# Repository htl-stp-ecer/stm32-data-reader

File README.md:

<div align="center">

# stm32-data-reader

**Raspberry Pi ↔ STM32 SPI bridge — reads sensor data and publishes it via LCM for RaccoonOS.**

> 📖 **Full documentation at [raccoon-docs.pages.dev](https://raccoon-docs.pages.dev/)**

</div>

---

This service runs on the Raspberry Pi inside the [KIPR Wombat](https://www.kipr.org/kipr/hardware-software) and acts as the hardware bridge between the STM32 microcontroller and the rest of RaccoonOS. It communicates with the STM32 over SPI, reads IMU, analog, and digital sensor data, and publishes everything onto the LCM multicast bus — where [RaccoonLib](https://github.com/htl-stp-ecer/raccoon-lib) and [botui](https://github.com/htl-stp-ecer/botui) can consume it. Motor and servo commands flow the other way: received from LCM and forwarded to the STM32.

---

## What it bridges

**Publishes (STM32 → LCM):**
- IMU — gyroscope, accelerometer, magnetometer, orientation quaternion, calibration accuracy
- Analog inputs (6 ports), digital inputs (16-bit)
- Motor back-EMF readings (4 ports)
- System — battery voltage, IMU temperature, CPU temperature

**Subscribes (LCM → STM32):**
- Motor power and stop commands (4 ports)
- Servo position commands (4 ports)
- BEMF reset, scale, and offset commands

Full channel reference: see [LCM Channels](#lcm-channels) below.

---

## Building

Reader and firmware are cross compiled for the Pi in Docker on your PC at native speed (no emulation). You only need Docker and Python 3.

```bash
python3 build.py                  # reader + firmware -> builds/stm32-data-reader_0.0_arm64.deb
python3 build.py --version 60     # release build (what CI does)
python3 build.py --test           # also build the unit tests and run them with qemu-user
python3 build.py --skip-firmware  # reuse the firmware of the last build
```

Output: `builds/stm32-data-reader_<version>_arm64.deb` (the reader, the STM32 firmware with its flash scripts, the systemd units) and `builds/manifest.json`. Measured: about 50 seconds from scratch (without cache), a few seconds with the cache.

### Local build (mock SPI, no hardware needed)

```bash
mkdir -p cmake-build-debug && cd cmake-build-debug
cmake .. -DUSE_SPI_MOCK=ON -DCMAKE_BUILD_TYPE=Debug
cmake --build . -j$(nproc)
```

| CMake option | Default | Description |
|:-------------|:--------|:------------|
| `USE_SPI_MOCK` | `ON` | Mock SPI — build and test without hardware |
| `CMAKE_BUILD_TYPE` | `Release` | `Release`, `Debug`, `RelWithDebInfo` |

---

## Deployment

### Install a release (recommended)

Each [release](https://github.com/htl-stp-ecer/stm32-data-reader/releases/latest) ships
`stm32-data-reader_<number>_arm64.deb`. `raccoon update` installs it, or on the Pi:

```bash
sudo apt install ./stm32-data-reader_<number>_arm64.deb
```

That installs the reader to `/usr/bin`, the firmware with its flash scripts to `/usr/lib/stm32-data-reader/firmware`, flashes the STM32 when the hardware is there and starts the services.

### Dev deploy (from source)

```bash
python3 deploy.py --host <your-pi-ip>     # installs builds/*.deb, flashes the firmware
```

`deploy.py` copies the `.deb` from `builds/` (made by `build.py`) to the Pi, sets `stm32-data-reader` to `dev` in `/etc/raccoon-bundle.json` (a deployed build is a custom build) and installs it with `apt`. The package installs the units, flashes the firmware and restarts the reader, so every deploy flashes the STM32 again.

### Running as a systemd service

```bash
sudo systemctl enable --now stm32_data_reader
journalctl -u stm32_data_reader -f
```

---

## Firmware

The STM32 firmware lives in `firmware/` and shares the SPI protocol header (`shared/spi/pi_buffer.h`) with the reader — single source of truth for both sides.

```bash
# Reader and firmware together, in Docker
python3 build.py

# Build firmware natively (requires gcc-arm-none-eabi)
cd firmware && mkdir -p build && cd build
cmake -G "Unix Makefiles" -DCMAKE_TOOLCHAIN_FILE=../CMake/GNU-ARM-Toolchain.cmake ..
cmake --build . -- -j$(nproc)
```

`python3 build.py` builds reader and firmware together (the firmware in `Dockerfile.firmware`). `python3 deploy.py --host <pi>` installs the package, which flashes the firmware to the STM32.

---

## Architecture

<div align="center">
  
</div>

| Component | What it does |
|:----------|:-------------|
| `Application` | Main orchestrator — lifecycle, signal handling |
| `DeviceController` | Owns SPI state: motors, servos, sensors |
| `DataPublisher` | Publishes sensor data to LCM with change detection |
| `CommandSubscriber` | Receives LCM commands and routes to DeviceController |
| `LcmBroker` | Typed publish/subscribe wrapper (PIMPL pattern) |
| `Spi` / `SpiMock` | Hardware abstraction toggled via `USE_SPI_MOCK` |

---

## LCM Channels

### Published (sensor data)

| Channel | Type | Description |
|:--------|:-----|:------------|
| `libstp/gyro/value` | `vector3f_t` | Gyroscope (rad/s) |
| `libstp/accel/value` | `vector3f_t` | Accelerometer (m/s²) |
| `libstp/mag/value` | `vector3f_t` | Magnetometer |
| `libstp/imu/quaternion` | `quaternion_t` | Orientation quaternion |
| `libstp/imu/temp/value` | `scalar_f_t` | IMU temperature (°C) |
| `libstp/cpu/temp/value` | `scalar_f_t` | CPU temperature (°C) |
| `libstp/battery/voltage` | `scalar_f_t` | Battery voltage |
| `libstp/analog/{0-5}/value` | `scalar_i32_t` | Analog sensor readings |
| `libstp/digital/{0-15}/value` | `scalar_i32_t` | Digital input states |
| `libstp/bemf/{0-3}/value` | `scalar_i32_t` | Motor back-EMF |
| `libstp/gyro/accuracy` | `scalar_i8_t` | Gyro calibration status (0–3) |
| `libstp/accel/accuracy` | `scalar_i8_t` | Accelerometer calibration status |
| `libstp/mag/accuracy` | `scalar_i8_t` | Magnetometer calibration status |
| `libstp/imu/quaternion_accuracy` | `scalar_i8_t` | Quaternion accuracy |

### Subscribed (commands)

| Channel | Type | Description |
|:--------|:-----|:------------|
| `libstp/motor/{0-3}/power_cmd` | `scalar_i32_t` | Motor power (−100 to 100) |
| `libstp/motor/{0-3}/stop_cmd` | `scalar_i32_t` | Stop motor |
| `libstp/servo/{0-3}/position_cmd` | `scalar_i32_t` | Servo position |
| `libstp/bemf/{0-3}/reset_cmd` | `scalar_i32_t` | Reset BEMF accumulator |
| `libstp/bemf/{0-3}/scale_cmd` | `scalar_f_t` | BEMF scale factor |
| `libstp/bemf/{0-3}/offset_cmd` | `scalar_f_t` | BEMF offset |
| `libstp/bemf/nominal_voltage_cmd` | `scalar_i32_t` | Nominal battery voltage |
| `libstp/system/dump_request` | `scalar_i32_t` | Request full data dump |

---

## Network setup for LCM

LCM uses UDP multicast. Enable the loopback route for local-only operation:

```bash
sudo systemctl enable --now lcm-loopback-multicast
# or manually:
sudo ip route add 239.255.76.67/32 dev lo
```

For network operation, ensure multicast is enabled and UDP port 7667 is open.

---

## Project structure

```
stm32-data-reader/
├── src/wombat/
│   ├── Application.cpp
│   ├── services/            # DataPublisher, CommandSubscriber, DeviceController
│   ├── hardware/            # Spi, SpiMock
│   ├── messaging/           # LcmBroker
│   └── core/                # Logger, Result<T>, utilities
├── include/wombat/          # Headers matching src/
├── shared/spi/pi_buffer.h   # SPI protocol (shared with STM32 firmware)
├── firmware/                # STM32 firmware source
├── lcm-messages/types/      # LCM message definitions (.lcm files)
├── systemd/                 # Service files
├── packaging/debian/        # control and maintainer scripts of the .deb
├── build.py                 # Cross-compiles reader + firmware in Docker, makes the .deb (builds/)
├── deploy.py                # Installs the .deb on a Pi (development)
├── Dockerfile               # aarch64 cross compiler for the reader
└── Dockerfile.firmware      # arm-none-eabi-gcc for the firmware
```

---

## Part of RaccoonOS

| Repository | What it is |
|:-----------|:-----------|
| [raccoon-lib](https://github.com/htl-stp-ecer/raccoon-lib) | Core robotics library — consumes LCM data published here |
| [raccoon-transport](https://github.com/htl-stp-ecer/raccoon-transport) | Shared LCM message types |
| [botui](https://github.com/htl-stp-ecer/botui) | Flutter UI — visualises sensor data from this service |
| [documentation](https://raccoon-docs.pages.dev/) | Full platform docs |

---

## License

Copyright (C) 2026 Tobias Madlberger  
Licensed under the GNU General Public License v3.0 — see [COPYING](COPYING) for details.

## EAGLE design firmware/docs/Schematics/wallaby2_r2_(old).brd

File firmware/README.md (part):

# Wombat Firmware

Bare-metal firmware for the **STM32F427VIT6** microcontroller on the KIPR Wombat robotics controller. The firmware
handles all real-time I/O: motor control (including PID), servo driving, sensor reading (analog, digital, IMU), and
communication with a Raspberry Pi companion over SPI.

## Table of Contents

- [System Overview](#system-overview)
- [Repository Structure](#repository-structure)
- [Building](#building)
- [Deploying and Flashing](#deploying-and-flashing)
- [Architecture](#architecture)
    - [Main Loop and Timing](#main-loop-and-timing)
    - [SPI Protocol](#spi-protocol)
    - [Motor Control](#motor-control)
    - [BEMF Sensing](#bemf-sensing)
    - [PID Controller](#pid-controller)
    - [Servo Control](#servo-control)
    - [IMU (MPU9250)](#imu-mpu9250)
    - [Analog and Digital Sensors](#analog-and-digital-sensors)
- [Hardware Pin Map](#hardware-pin-map)
- [Clock Configuration](#clock-configuration)
- [Companion: STM32 Data Reader](#companion-stm32-data-reader)
- [Adding or Changing a Peripheral](#adding-or-changing-a-peripheral)
- [Common Pitfalls](#common-pitfalls)
- [Authors and Contributors](#authors-and-contributors)

---

## System Overview

```mermaid
graph TD
    Pi["<b>Raspberry Pi</b><br/>stm32-data-reader service<br/>C++ · LCM pub/sub"]
    SPI["SPI2 full-duplex · 20 MHz<br/>/dev/spidev0.0"]
    STM["<b>STM32F427VIT6</b><br/>This firmware · 180 MHz · Bare-metal"]

    MOT["Motors (4)<br/>25 kHz PWM · 200 Hz PID"]
    SRV["Servos (4)<br/>50 Hz PWM · 10 Hz update"]
    ADC["ADC (6 + batt)<br/>1 kHz sample + 200 Hz BEMF"]
    IMU["IMU · MPU9250<br/>SPI3 · 50 Hz DMP · 9-axis"]

    Pi <--> SPI <--> STM
    STM --- MOT
    STM --- SRV
    STM --- ADC
    STM --- IMU
```

The STM32 runs a bare-metal super-loop. All timing is interrupt-driven from a 1 MHz system timer (TIM6). The Pi sends
commands and receives sensor data via a continuously-running circular SPI DMA transfer.

---

## Repository Structure

```
Firmware-Stp/
├── CMakeLists.txt          # Root CMake config (project "wombat")
├── build.sh                # Local build: clean + cmake + make
├── deploy.sh               # Docker build + SCP + flash via SSH
├── Dockerfile              # ARM cross-compile environment
├── CMake/
│   └── GNU-ARM-Toolchain.cmake
├── Firmware/               # All firmware source code
│   ├── CMakeLists.txt      # Firmware build target (wombat.elf → .bin)
│   ├── Startup/
│   │   └── startup_stm32f427vitx.s
│   ├── include/
│   │   ├── main.h          # Pin defines, HAL handles, Error_Handler
│   │   ├── Actors/
│   │   │   ├── motor.h     # Motor structs, direction enum, control API
│   │   │   ├── pid.h       # PID controller struct and functions
│   │   │   └── servo.h     # Servo structs and modes
│   │   ├── Communication/
│   │   │   ├── pi_buffer_struct.h      # TxBuffer / RxBuffer (shared with Pi)
│   │   │   ├── communication_with_pi.h # TRANSFER_VERSION, extern buffers
│   │   │   └── spi.h                   # SPI2 (Pi) and SPI3 (IMU) init
│   │   ├── Sensors/
│   │   │   ├── bemf.h          # BEMF state machine, timing constants
│   │   │   ├── adcInit.h       # ADC1/ADC2 init
│   │   │   ├── adcPorts-batteryVoltage.h
│   │   │   ├── digitalPorts.h
│   │   │   └── IMU/            # MPU9250 driver, DMP, config
│   │   ├── Hardware/
│   │   │   ├── gpio.h / dma.h / timer.h / timerInit.h
│   │   │   └── interupt_prioryty.h     # All IRQ priority constants
│   │   └── Data_structures/
│   │       └── filter.h        # Inline low-pass filter
│   └── src/
│       ├── main.c              # Entry point, super-loop
│       ├── Actors/
│       │   ├── motor.c         # Motor control: mode dispatch, PID integration
│       │   ├── pid.c           # PID algorithm with anti-windup
│       │   └── servo.c         # Servo update, 6V enable
│       ├── Communication/
│       │   ├── communication_with_pi.c  # Buffer init, DMA start
│       │   └── spi.c                    # SPI2/SPI3 config, DMA callback
│       ├── Sensors/
│       │   ├── bemf.c                   # BEMF measurement + position accumulation
│       │   ├── adcPorts-batteryVoltage.c
│       │   ├── adcInit.c
│       │   ├── digitalPorts.c
│       │   └── IMU/                     # imu.c, MPU9250.c, mpu9250_hal.c, mpu9250_dmp.c
│       └── Hardware/
│           ├── gpio.c / dma.c / timer.c / timerInit.c
│           └── stm32f4xx_it.c           # All ISR handlers
├── libs/
│   ├── CMSIS/                  # ARM Cortex-M4 headers
│   ├── STM32F4xx_HAL_Driver/   # ST HAL library
│   └── motion_driver_6.12/     # InvenSense eMD 6.12 + MPL prebuilt binary
├── linker/
│   ├── STM32F427VITx_FLASH.ld
│   └── STM32F427VITx_RAM.ld
├── docs/
│   ├── Datasheets/
│   ├── Schematics/
│   └── Wombat_BOM_rev4.xlsx
└── flashFiles/                 # Scripts for flashing from the Pi
```

---

## Building

### Prerequisites

- ARM GCC toolchain (`arm-none-eabi-gcc`) in PATH, **or** Docker
- CMake 3.24+

### Local Build

```bash
./build.sh
```

This deletes `build/`, runs CMake with the ARM toolchain file, and builds. Output: `build/Firmware/wombat.bin`.

### Docker Build

```bash
docker compose up --build
```

The container cross-compiles and places the binary in `build/`.

---

## Deploying and Flashing

```bash
# Set the Pi IP (default 10.101.156.14)
export RPI_HOST=<pi-ip>

./deploy.sh
```

This will:

1. Build inside Docker
2. SCP `wombat.bin` and flash scripts to the Pi
3. Stop `stm32_data_reader.service`
4. Flash the STM32 via `flash_wombat.sh`
5. Restart `stm32_data_reader.service`

---

## Architecture

### Main Loop and Timing

The firmware is bare-metal (no RTOS). The `main()` function initializes all peripherals in order, then enters an
infinite loop:

```mermaid
flowchart TD
    A[HAL_Init] --> B[SystemClock_Config]
    B --> C["GPIO · DMA · ADC1 · ADC2<br/>SPI2 · SPI3<br/>TIM1 · TIM3 · TIM6 · TIM8 · TIM9"]
    C --> D[systemTimerStart]
    D --> E[initPiCommunication]
    E --> F[initMotors]
    F --> G[setupImu]
    G --> H{"while(1)"}

    H -->|every 100 ms| I["update_servo_cmd()"]
    H -->|PID_SPEED flag| J["update_motor_pidSettings()"]
    H -->|PID_POS flag| K["update_motor_posPidSettings()"]
    H -->|continuously| L["readImu() · ~50 Hz"]
    H -->|continuously| M["updatingAnalogValuesInSpiBuffer()"]
    H -->|continuously| N["updatingMotorsInSpiBuffer()"]

    I & J & K & L & M & N --> H
```

**TIM6 (1 MHz system timer)** drives all periodic sampling from its ISR:

| Interval                | Action                                            |
|-------------------------|---------------------------------------------------|
| Every 5000 us           | `stop_motors_for_bemf_conv()` - begins BEMF cycle |
| 500 us after BEMF start | `startBemfReading()` - triggers ADC2 DMA          |
| Every 1000 us           | `sampleAnalogPorts()` - triggers ADC1 DMA         |

When ADC2 completes (DMA interrupt), `processBEMF()` runs immediately, followed by `update_motor()` for all 4 channels.
This makes the **motor PID run at exactly 200 Hz**.

### SPI Protocol

The STM32 operates as an SPI slave on SPI2, communicating with the Pi using continuous circular DMA. Both sides exchange
a fixed-size buffer simultaneously on every transfer.

**Configuration:** Mode 1 (CPOL=0, CPHA=1), 8-bit, MSB first, hardware NSS.

**Transfer version:** Both sides must agree on `TRANSFER_VERSION` (currently **6**). A mismatch causes the Pi reader to
retry and eventually reset the STM32.

**Buffer size:** `max(sizeof(TxBuffer), sizeof(RxBuffer))` bytes per direction.

#### TxBuffer (STM32 → Pi)

```c
typedef struct __attribute__((packed)) {
    uint8_t    transferVersion;       // Must equal TRANSFER_VERSION
    uint32_t   updateTime;            // Microsecond timestamp
    MotorData  motor;                 // .bemf[4], .position[4]
    int16_t    analogSensor[6];       // 6 analog input ports
    int16_t    batteryVoltage;        // Raw 12-bit ADC, 11x voltage divider
    uint16_t   digitalSensors;        // Bits 0-9: DIN ports, bit 10: button
    ImuData    imu;                   // Gyro, accel, compass, linearAccel,
                                      // accelVelocity, quaternion, temperature
} TxBuffer;
```

#### RxBuffer (Pi → STM32)

```c
typedef struct __attribute__((packed)) {
    uint8_t          transferVersion;
    uint32_t         updates;             // Update flags + parity (bit 7)
    uint8_t          systemShutdown;      // Bit 0: servos, bit 1: motors
    uint16_t         motorControlMode;    // 3 bits per motor (see Motor Control)
    int32_t          motorTarget[4];      // Meaning depends on control mode
    int32_t          motorGoalPosition[4];// Target position for MTP mode
    uint8_t          servoMode;           // 2 bits per servo
    uint16_t         servoPos[4];         // Servo pulse width
    MotorPidSettings motorPidSettings;    // Runtime-adjustable PID gains
} RxBuffer;
```

#### Update Flags

The `updates` field uses even parity to guard against corrupted transfers:

| Flag                               | Value  | Effect                       |
|------------------------------------|--------|------------------------------|
| `PI_BUFFER_UPDATE_MOTOR_PID_SPEED` | `0x01` | Apply new velocity PID gains |
| `PI_BUFFER_UPDATE_MOTOR_PID_POS`   | `0x02` | Apply new position PID gains |
| `PI_BUFFER_UPDATE_PARITY_BIT`      | `0x80` | Even parity check bit        |

Updates are only applied when the parity check passes (`updates % 2 == 1`). The Pi clears all flags after each transfer.

### Motor Control

4 DC motors driven by H-bridges with 25 kHz PWM. Each motor has 3 bits in `motorControlMode`:

| Mode          | Value   | Behavior                                                                                                       |
|---------------|---------|----------------------------------------------------------------------------------------------------------------|
| OFF           | `0b000` | Direction pins low, PWM = 0                                                                                    |
| PASSIVE_BRAKE | `0b001` | Both direction pins high (short-brake), PWM = 0                                                                |
| PWM           | `0b010` | Direct duty cycle from `motorTarget[ch]` (0-399)                                                               |
| MAV           | `0b011` | Move At Velocity - PID velocity control. `motorTarget` = velocity setpoint                                     |
| MTP           | `0b100` | Move To Position - cascaded position + velocity PID. `motorGoalPosition` = target, `motorTarget` = speed limit |

**Direction** is derived from the PID output sign: positive = CW (D1 high), negative = CCW (D0 high).

**Mode changes** automatically reset both PID controllers and the MTP hold state.

**Position hold** (MTP only): there is no done flag. Within `MTP_DONE_THRESHOLD` (3) BEMF ticks of the goal the motor
brakes and keeps holding; if it is pushed more than `MTP_HOLD_RELEASE` (8) ticks away it is driven back with a fresh
profile. MTP stays active until another mode is commanded. Clients detect arrival via the position channel.

### BEMF Sensing

Back-EMF is used both as a speed measurement (for velocity PID) and accumulated as a position estimate. The measurement
cycle runs at 200 Hz:

```mermaid
flowchart LR
    A["TIM6 ISR<br/>every 5000 us"] -->|"stop_motors_for_bemf_conv()"| B["All motor<br/>direction pins → OFF"]
    B -->|"wait 500 us"| C["startBemfReading()<br/>ADC2 DMA · 8 channels"]
    C -->|"DMA complete IRQ"| D["processBEMF()"]
    D --> E["BEMFH − BEMFL per motor<br/>→ low-pass filter α=0.2"]
    E -->|"|filtered| > 8"| F["Accumulate into<br/>position counter"]
    E -->|"filtered > 1700"| G["Discard<br/>out-of-range"]
    F --> H["update_motor()<br/>PID + restore direction"]
    G --> H
```

1. **Stop motors** - all direction pins to OFF to allow back-EMF to appear
2. **Wait 500 us** for the signal to stabilize
3. **Start ADC2** DMA conversion across 8 channels (2 differential per motor: BEMFH - BEMFL)
4. **Process** in the ADC completion ISR: compute differential, filter, accumulate position
5. **Resume motors** - direction pins restored by `update_motor()`

### PID Controller

Two independent loops per motor, cascaded in MTP mode:

```mermaid
flowchart LR
    GP["Goal Position"] --> PPID["Position PID<br/>Kp=0.01 · Ki=0 · Kd=0.015"]
    CP["Current Position<br/>(accumulated BEMF)"] --> PPID
    PPID -->|"velocity target<br/>(clamped by motorTarget)"| VPID
    GV["Goal Velocity<br/>(MAV mode)"] -.-> VPID["Velocity PID<br/>Kp=1.22 · Ki=0.045 · Kd=0"]
    BEMF["BEMF reading<br/>(200 Hz)"] --> VPID
    VPID -->|"PWM duty<br/>(0–399)"| MOT["Motor H-bridge"]
```

**Velocity loop (inner):** Runs every BEMF cycle (200 Hz). Directly outputs a PWM duty cycle.

| Parameter | Default                                          |
|-----------|--------------------------------------------------|
| Kp        | 1.22                                             |
| Ki        | 0.045                                            |
| Kd        | 0.0                                              |
| iMax      | 399 (anti-windup clamp on integral contribution) |
| outMax    | 399 (output clamp = max duty cycle)              |

**Position loop (outer, MTP mode only):** Outputs a velocity target for the inner loop.

| Parameter | Default |
|-----------|---------|
| Kp        | 0.01    |
| Ki        | 0.0     |
| Kd        | 0.015   |

**Anti-windup:** The integral *contribution* (`Ki * accumulated_error`) is clamped, and the raw accumulator is
back-calculated to prevent drift:

```c
float iTerm = pid->kI * pid->iErr;
if (iTerm > pid->iMax) { iTerm = pid->iMax; pid->iErr = pid->iMax / pid->kI; }
```

All gains can be overridden at runtime from the Pi via `MotorPidSettings` in the RxBuffer.

### Servo Control

4 standard hobby servos at 50 Hz PWM. Each servo has a 2-bit mode in `servoMode`:

| Mode           | Value | Behavior                                                     |
|----------------|-------|--------------------------------------------------------------|
| FULLY_DISABLED | 0     | PWM off, 6V supply disabled if all servos are fully disabled |
| DISABLED       | 1     | PWM off for this servo, but 6V supply stays on               |
| ENABLED        | 2     | PWM active at the position in `servoPos[n]`                  |

The 6V servo power supply (PE10) is enabled when any servo is not FULLY_DISABLED.

Servo positions update at 10 Hz to avoid jitter from SPI timing variations.

### IMU (MPU9250)

The MPU9250 9-axis IMU is connected via SPI3 (firmware is master). It uses the InvenSense embedded Motion Driver (eMD)
6.12 stack with DMP firmware:

- **DMP features:** 6-axis low-power quaternion, raw accelerometer, calibrated gyroscope, gyro auto-calibration
- **MPL features:** 9-axis sensor fusion, fast no-motion detection, gyro temperature compensation, vector compass
  calibration, magnetic disturbance detection
- **Output rates:** 50 Hz gyro/accel, 10 Hz compass, 0.5 Hz temperature
- **Self-test:** Run at startup, biases applied to hardware offset registers

Data extracted into `txBuffer.imu`:

| Field           | Type     | Units                                      |
|-----------------|----------|--------------------------------------------|
| `gyro`          | float[3] | rad/s                                      |
| `accel`         | float[3] | m/s^2                                      |
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
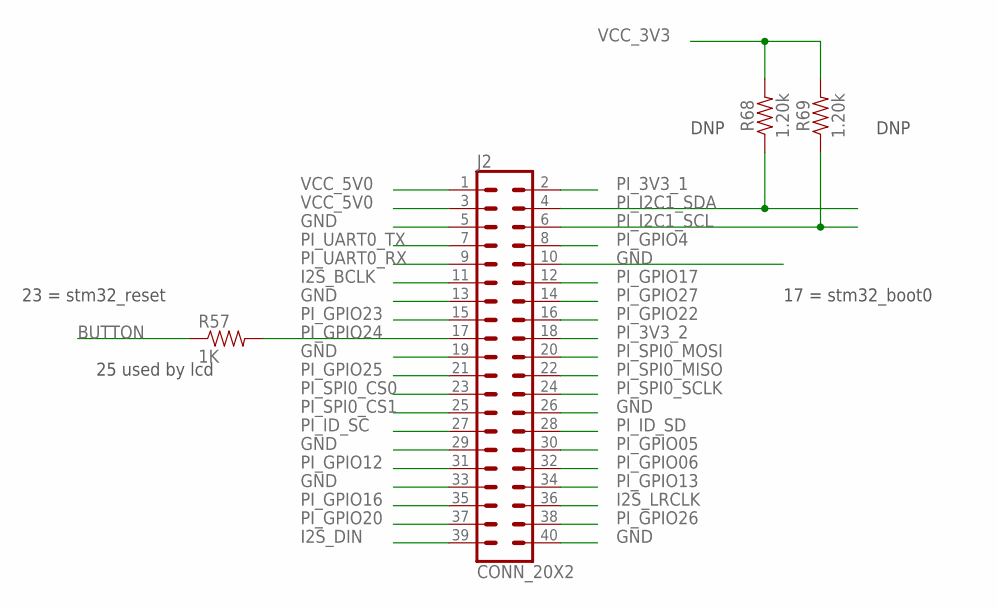
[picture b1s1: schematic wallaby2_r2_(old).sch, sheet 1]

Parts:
J2: CONN_20X2; 2X20
R57: 1K; 0603-RES
R68, R69: 1.20k; 0603

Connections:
BUTTON: R57.1; also elsewhere on the board
GND: J2.5, J2.10, J2.13, J2.19, J2.26, J2.29, J2.33, J2.40; also elsewhere on the board
I2S_BCLK: J2.11; also elsewhere on the board
I2S_DIN: J2.39; also elsewhere on the board
I2S_LRCLK: J2.36; also elsewhere on the board
PI_3V3_1: J2.2
PI_3V3_2: J2.18
PI_GPIO4: J2.8
PI_GPIO05: J2.30
PI_GPIO06: J2.32
PI_GPIO12: J2.31
PI_GPIO13: J2.34
PI_GPIO16: J2.35
PI_GPIO17: J2.12; also elsewhere on the board
PI_GPIO20: J2.37
PI_GPIO22: J2.16
PI_GPIO23: J2.15; also elsewhere on the board
PI_GPIO24: J2.17, R57.2
PI_GPIO25: J2.21; also elsewhere on the board
PI_GPIO26: J2.38
PI_GPIO27: J2.14
PI_I2C1_SCL: J2.6, R69.1; also elsewhere on the board
PI_I2C1_SDA: J2.4, R68.1; also elsewhere on the board
PI_ID_SC: J2.27
PI_ID_SD: J2.28
PI_SPI0_CS0: J2.23; also elsewhere on the board
PI_SPI0_CS1: J2.25
PI_SPI0_MISO: J2.22; also elsewhere on the board
PI_SPI0_MOSI: J2.20; also elsewhere on the board
PI_SPI0_SCLK: J2.24; also elsewhere on the board
PI_UART0_RX: J2.9; also elsewhere on the board
PI_UART0_TX: J2.7; also elsewhere on the board
VCC_3V3: R68.2, R69.2; also elsewhere on the board
VCC_5V0: J2.1, J2.3; also elsewhere on the board

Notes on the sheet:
25 used by lcd
23 = stm32_reset
17 = stm32_boot0
DNP

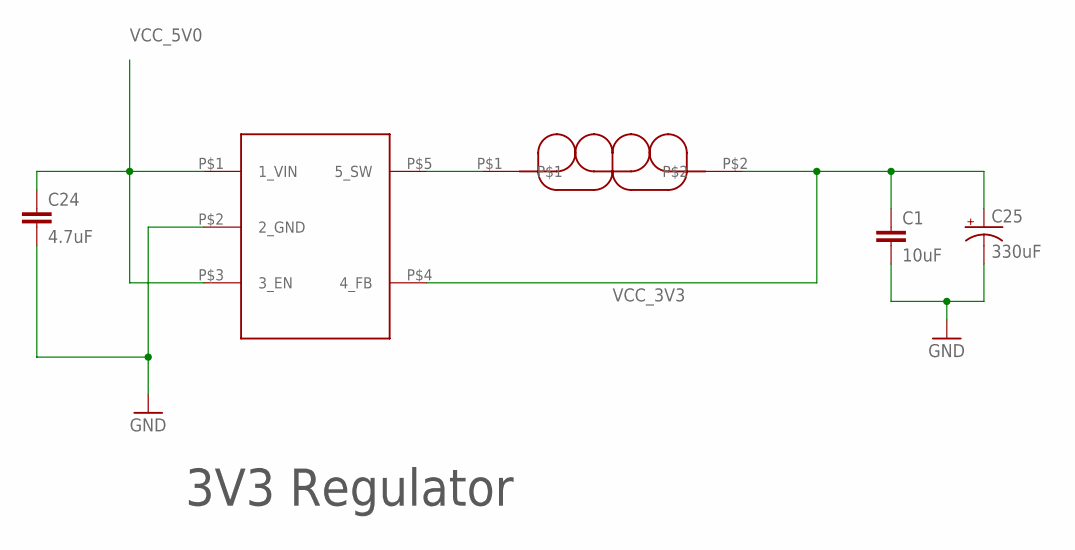
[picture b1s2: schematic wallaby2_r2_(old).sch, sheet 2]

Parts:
C1: 10uF; 0603-CAP
C24: 4.7uF; 0603-CAP
C25: 330uF; PANASONIC_D
U7: LM3671; SOT-23-5
U8: 2.2uH; 3P2MM-X-3P2MM-INDUCTOR

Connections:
GND: C1.2, C24.2, C25.-, U7.P$2 (2_GND); also elsewhere on the board
unnamed: U7.P$5 (5_SW), U8.P$1
VCC_3V3: C1.1, C25.+, U7.P$4 (4_FB), U8.P$2; also elsewhere on the board
VCC_5V0: C24.1, U7.P$1 (1_VIN), U7.P$3 (3_EN); also elsewhere on the board

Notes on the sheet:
3V3 Regulator

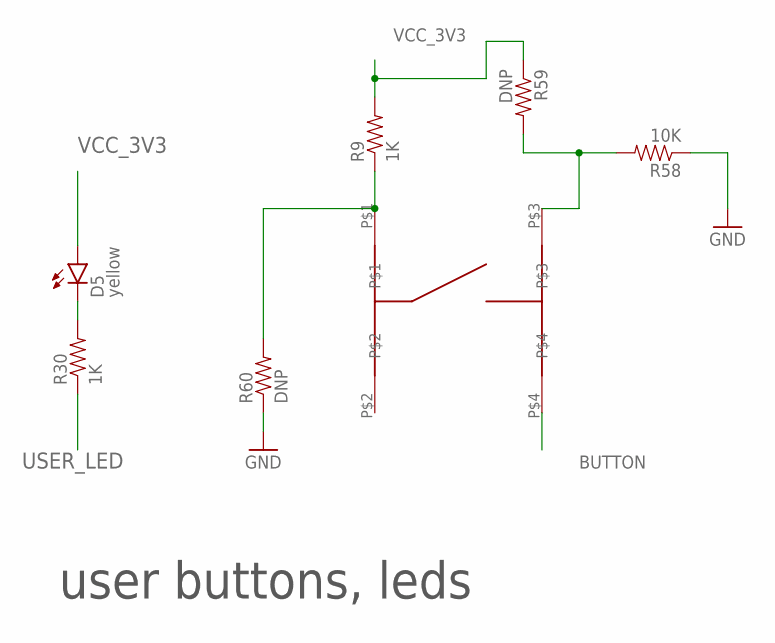
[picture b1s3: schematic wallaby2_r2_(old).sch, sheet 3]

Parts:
D5: yellow; LED-0603
R9, R30: 1K; 0603-RES
R58: 10K; 0603-RES
R59, R60: DNP; 0603-RES
U75: PUSHBUTTON-1571527-2; BUTTON-1571527-2

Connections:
BUTTON: U75.P$4; also elsewhere on the board
GND: R58.1, R60.1; also elsewhere on the board
unnamed: D5.C, R30.2
unnamed: R9.1, R60.2, U75.P$1
unnamed: R58.2, R59.2, U75.P$3
USER_LED: R30.1; also elsewhere on the board
VCC_3V3: D5.A, R9.2, R59.1; also elsewhere on the board

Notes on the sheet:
user buttons, leds

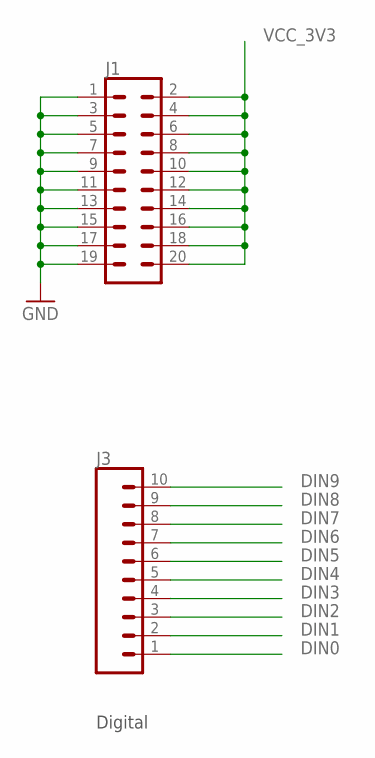
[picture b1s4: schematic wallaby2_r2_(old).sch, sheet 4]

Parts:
J1: CONN_10X2; 2X10
J3: CONN_10"; 1X10

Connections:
DIN0: J3.1; also elsewhere on the board
DIN1: J3.2; also elsewhere on the board
DIN2: J3.3; also elsewhere on the board
DIN3: J3.4; also elsewhere on the board
DIN4: J3.5; also elsewhere on the board
DIN5: J3.6; also elsewhere on the board
DIN6: J3.7; also elsewhere on the board
DIN7: J3.8; also elsewhere on the board
DIN8: J3.9; also elsewhere on the board
DIN9: J3.10; also elsewhere on the board
GND: J1.1, J1.3, J1.5, J1.7, J1.9, J1.11, J1.13, J1.15, J1.17, J1.19; also elsewhere on the board
VCC_3V3: J1.2, J1.4, J1.6, J1.8, J1.10, J1.12, J1.14, J1.16, J1.18, J1.20; also elsewhere on the board

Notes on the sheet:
Digital

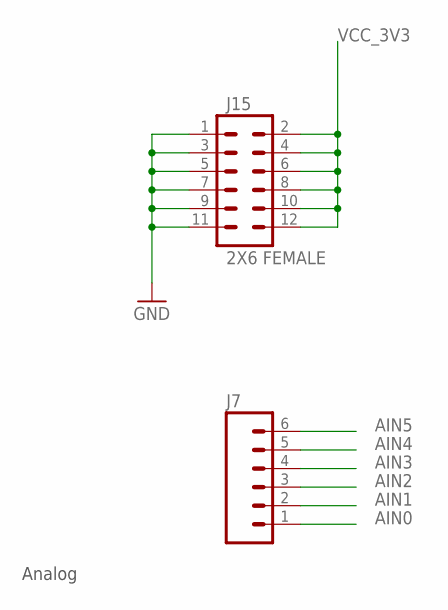
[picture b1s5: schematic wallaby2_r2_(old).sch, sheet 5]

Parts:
J7: M06SILK_FEMALE_PTH; 1X06
J15: 2X6 FEMALE; 2X6

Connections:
AIN0: J7.1; also elsewhere on the board
AIN1: J7.2; also elsewhere on the board
AIN2: J7.3; also elsewhere on the board
AIN3: J7.4; also elsewhere on the board
AIN4: J7.5; also elsewhere on the board
AIN5: J7.6; also elsewhere on the board
GND: J15.1, J15.3, J15.5, J15.7, J15.9, J15.11; also elsewhere on the board
VCC_3V3: J15.2, J15.4, J15.6, J15.8, J15.10, J15.12; also elsewhere on the board

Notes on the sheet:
Analog

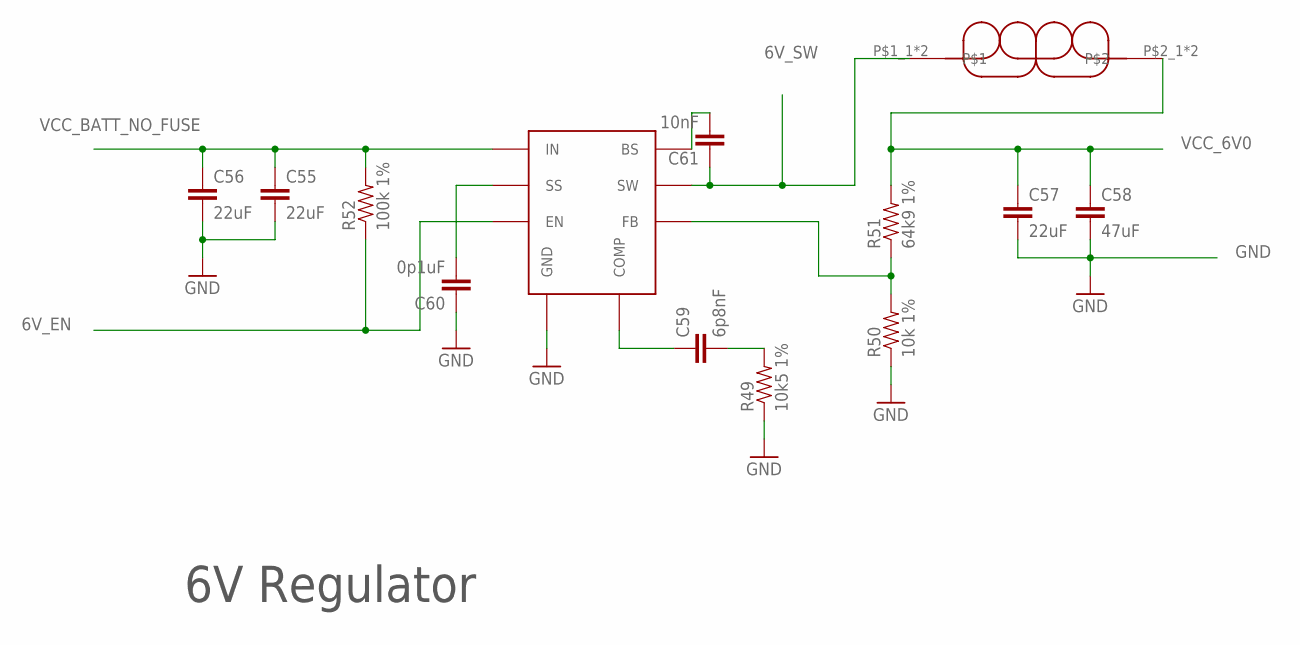
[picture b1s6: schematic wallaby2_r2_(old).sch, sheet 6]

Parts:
C55, C56, C57: 22uF; 1210@1
C58: 47uF; 1210@1
C59: 6p8nF; 0603-CAP
C60: 0p1uF; 0603-CAP
C61: 10nF; 0603-CAP
L2: 6.5uH; INDUCT-3232-1050
R49: 10k5 1%; 0603-RES
R50: 10k 1%; 0603-RES
R51: 64k9 1%; 0603-RES
R52: 100k 1%; 0603-RES
U72: AP65502; SO-8EP

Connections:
6V_EN: R52.1, U72.7 (EN); also elsewhere on the board
6V_SW: C61.1, L2.P$1_1, L2.P$1_2, U72.3 (SW)
GND: C55.2, C56.2, C57.2, C58.2, C60.1, R49.1, R50.1, U72.4 (GND), U72.GND, U72.V$1 (GND), U72.V$2 (GND), U72.V$3 (GND), U72.V$4 (GND), U72.V$5 (GND), U72.V$6 (GND), U72.V$7 (GND), U72.V$8 (GND), U72.V$9 (GND), U72.V$10 (GND), U72.V$11 (GND), U72.V$12 (GND), U72.V$13 (GND), U72.V$14 (GND), U72.V$15 (GND); also elsewhere on the board
unnamed: C61.2, U72.1 (BS)
unnamed: C59.1, U72.6 (COMP)
unnamed: C59.2, R49.2
unnamed: C60.2, U72.8 (SS)
unnamed: R50.2, R51.1, U72.5 (FB)
VCC_6V0: C57.1, C58.1, L2.P$2_1, L2.P$2_2, R51.2; also elsewhere on the board
VCC_BATT_NO_FUSE: C55.1, C56.1, R52.2, U72.2 (IN); also elsewhere on the board

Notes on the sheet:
6V Regulator

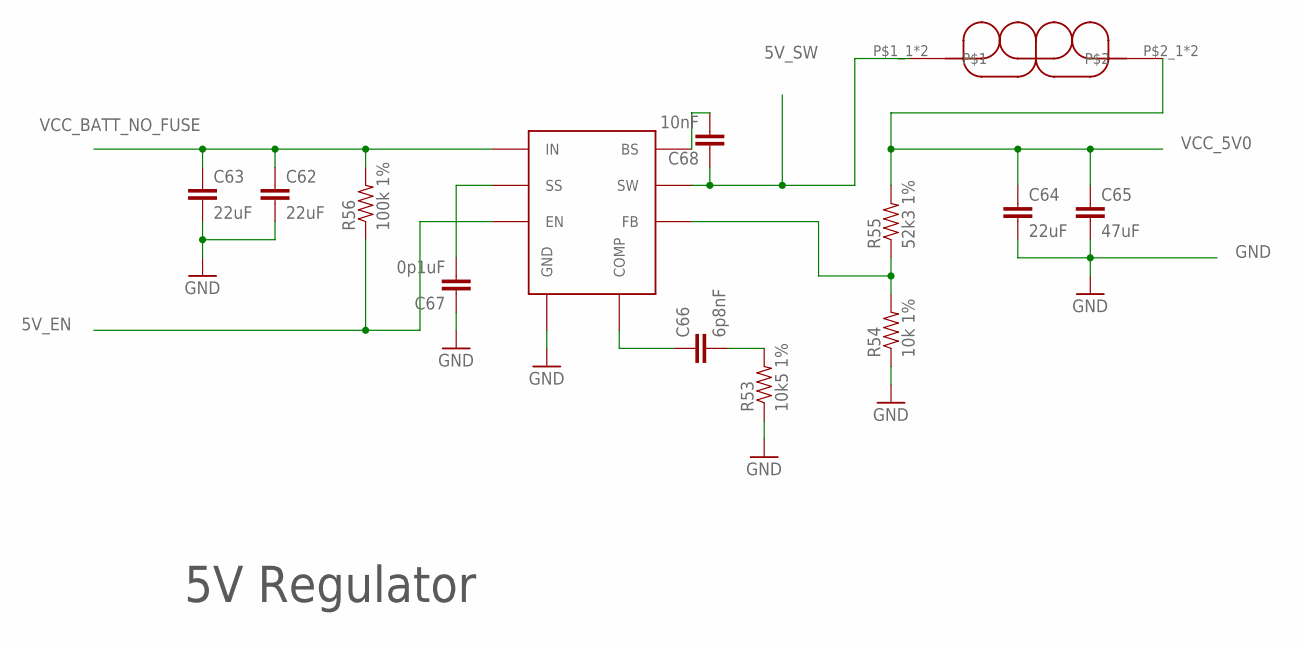
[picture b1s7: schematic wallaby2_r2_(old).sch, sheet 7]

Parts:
C62, C63, C64: 22uF; 1210@1
C65: 47uF; 1210@1
C66: 6p8nF; 0603-CAP
C67: 0p1uF; 0603-CAP
C68: 10nF; 0603-CAP
L4: 6.5uH; INDUCT-3232-1050
R53: 10k5 1%; 0603-RES
R54: 10k 1%; 0603-RES
R55: 52k3 1%; 0603-RES
R56: 100k 1%; 0603-RES
U73: AP65502; SO-8EP

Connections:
5V_EN: R56.1, U73.7 (EN)
5V_SW: C68.1, L4.P$1_1, L4.P$1_2, U73.3 (SW)
GND: C62.2, C63.2, C64.2, C65.2, C67.1, R53.1, R54.1, U73.4 (GND), U73.GND, U73.V$1 (GND), U73.V$2 (GND), U73.V$3 (GND), U73.V$4 (GND), U73.V$5 (GND), U73.V$6 (GND), U73.V$7 (GND), U73.V$8 (GND), U73.V$9 (GND), U73.V$10 (GND), U73.V$11 (GND), U73.V$12 (GND), U73.V$13 (GND), U73.V$14 (GND), U73.V$15 (GND); also elsewhere on the board
unnamed: C68.2, U73.1 (BS)
unnamed: C66.1, U73.6 (COMP)
unnamed: C66.2, R53.2
unnamed: C67.2, U73.8 (SS)
unnamed: R54.2, R55.1, U73.5 (FB)
VCC_5V0: C64.1, C65.1, L4.P$2_1, L4.P$2_2, R55.2; also elsewhere on the board
VCC_BATT_NO_FUSE: C62.1, C63.1, R56.2, U73.2 (IN); also elsewhere on the board

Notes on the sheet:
5V Regulator

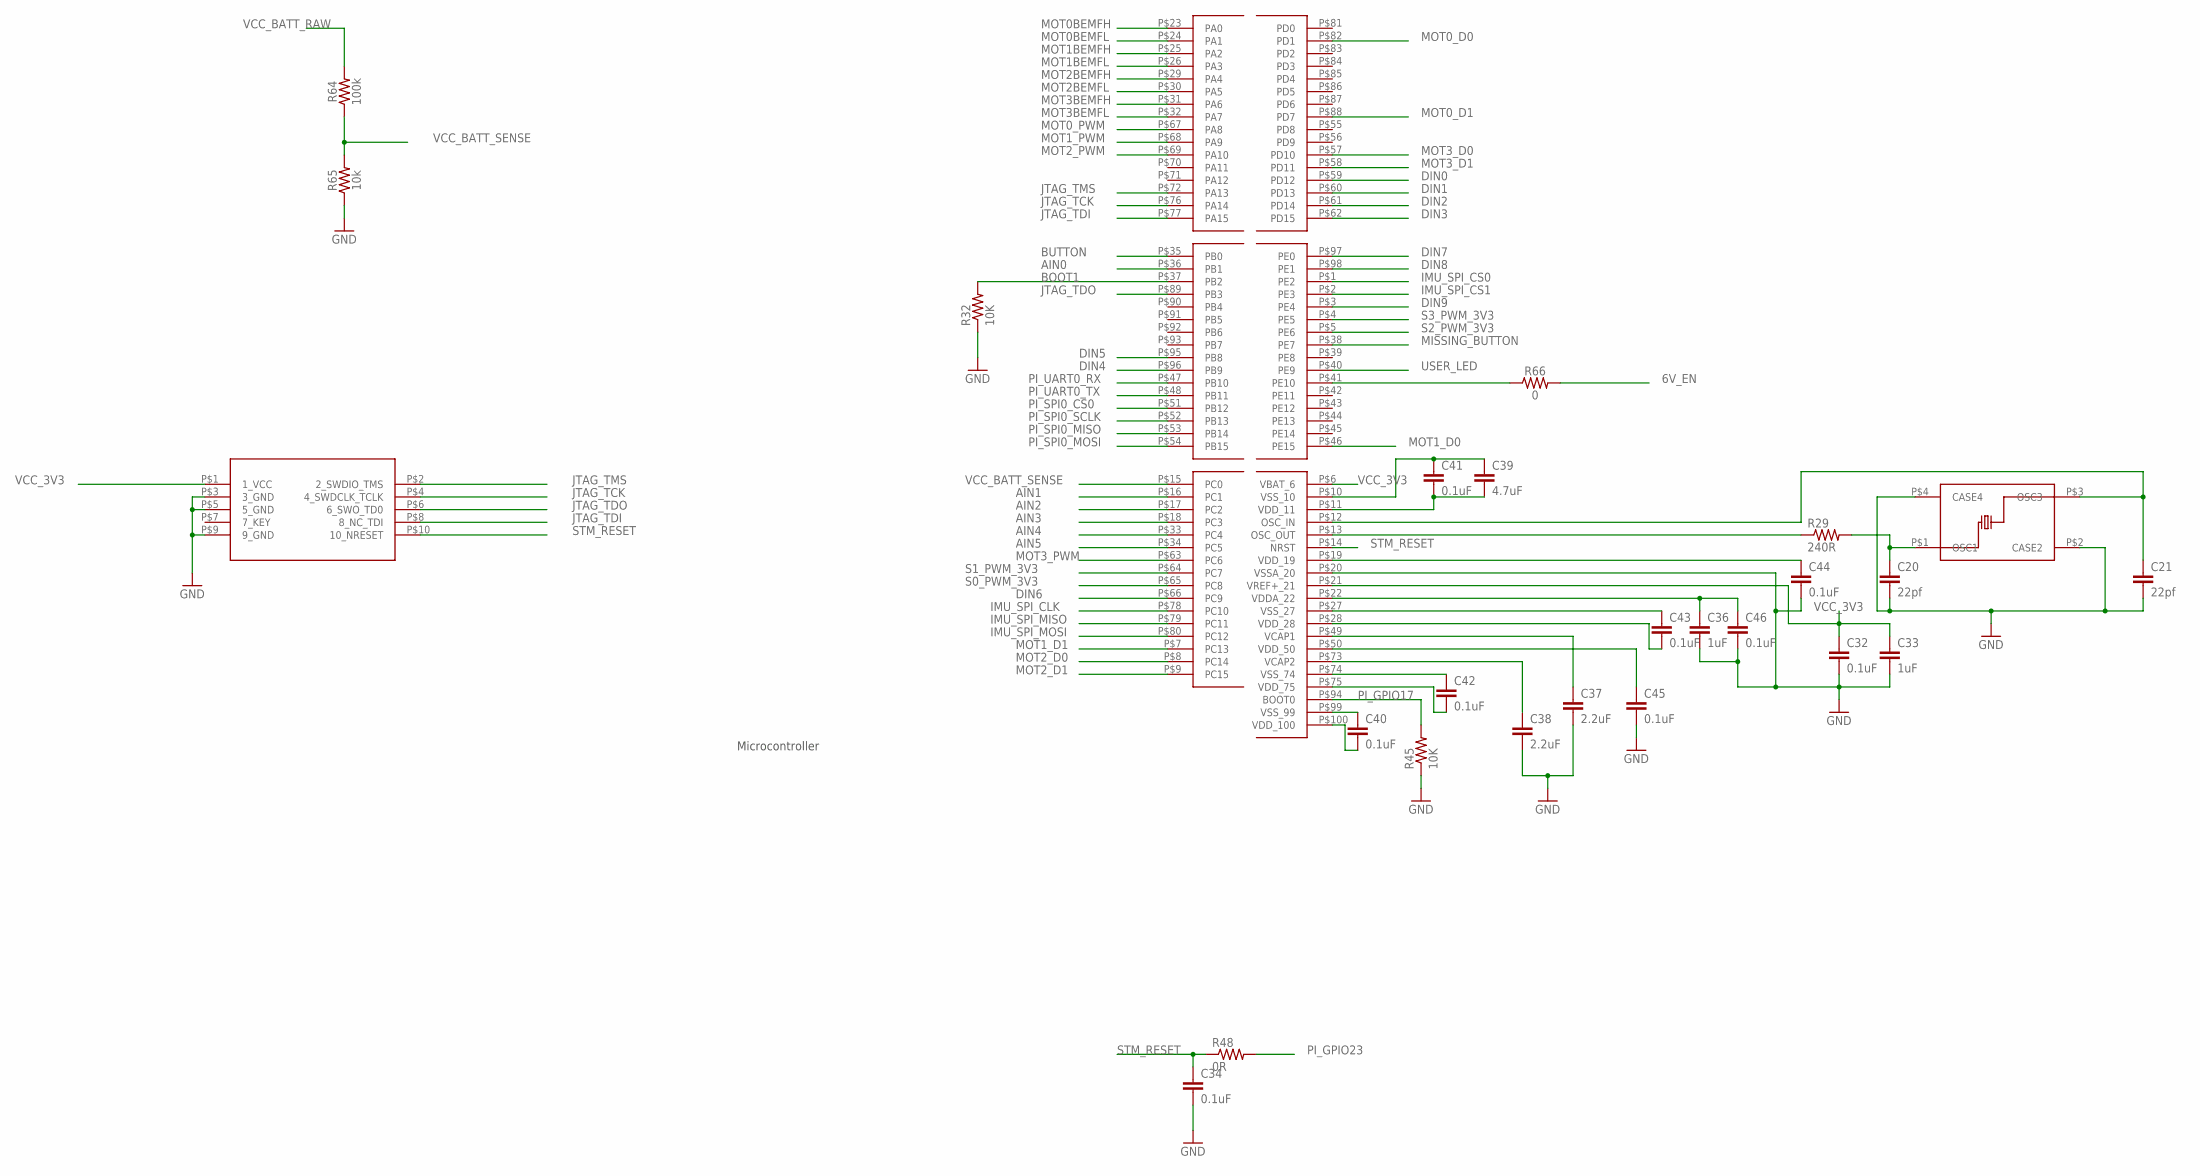
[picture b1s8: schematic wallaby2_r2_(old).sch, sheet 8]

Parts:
C20, C21: 22pf; 0603-CAP
C32, C34, C40, C41, C42, C43, C44, C45, C46: 0.1uF; 0603-CAP
C33, C36: 1uF; 0603-CAP
C37, C38: 2.2uF; 0603-CAP
C39: 4.7uF; 0603-CAP
R29: 240R; 0603-RES
R32, R45: 10K; 0603-RES
R48: 0R; 0603-RES
R64: 100k; 0603
R65: 10k; 0603
R66: 0; 0603
U37: STM32F427VIT6; LQFP-100
U38: TSX-3325; TSX-3225
U39: CORTEX_JTAG; CORTEX-JTAG-HDR

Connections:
6V_EN: R66.2; also elsewhere on the board
AIN0: U37.P$36 (PB1); also elsewhere on the board
AIN1: U37.P$16 (PC1); also elsewhere on the board
AIN2: U37.P$17 (PC2); also elsewhere on the board
AIN3: U37.P$18 (PC3); also elsewhere on the board
AIN4: U37.P$33 (PC4); also elsewhere on the board
AIN5: U37.P$34 (PC5); also elsewhere on the board
BOOT1: R32.2, U37.P$37 (PB2)
BUTTON: U37.P$35 (PB0); also elsewhere on the board
DIN0: U37.P$59 (PD12); also elsewhere on the board
DIN1: U37.P$60 (PD13); also elsewhere on the board
DIN2: U37.P$61 (PD14); also elsewhere on the board
DIN3: U37.P$62 (PD15); also elsewhere on the board
DIN4: U37.P$96 (PB9); also elsewhere on the board
DIN5: U37.P$95 (PB8); also elsewhere on the board
DIN6: U37.P$66 (PC9); also elsewhere on the board
DIN7: U37.P$97 (PE0); also elsewhere on the board
DIN8: U37.P$98 (PE1); also elsewhere on the board
DIN9: U37.P$3 (PE4); also elsewhere on the board
GND: C20.2, C21.2, C32.2, C33.2, C34.2, C36.2, C37.2, C38.2, C39.1, C40.1, C41.1, C42.1, C43.1, C44.2, C45.2, C46.2, R32.1, R45.1, R65.1, U37.P$10 (VSS_10), U37.P$20 (VSSA_20), U37.P$27 (VSS_27), U37.P$74 (VSS_74), U37.P$99 (VSS_99), U38.P$2 (CASE2), U38.P$4 (CASE4), U39.P$3 (3_GND), U39.P$5 (5_GND), U39.P$9 (9_GND); also elsewhere on the board
IMU_SPI_CLK: U37.P$78 (PC10); also elsewhere on the board
IMU_SPI_CS0: U37.P$1 (PE2); also elsewhere on the board
IMU_SPI_CS1: U37.P$2 (PE3)
IMU_SPI_MISO: U37.P$79 (PC11); also elsewhere on the board
IMU_SPI_MOSI: U37.P$80 (PC12); also elsewhere on the board
JTAG_TCK: U37.P$76 (PA14), U39.P$4 (4_SWDCLK_TCLK)
JTAG_TDI: U37.P$77 (PA15), U39.P$8 (8_NC_TDI)
JTAG_TDO: U37.P$89 (PB3), U39.P$6 (6_SWO_TD0)
JTAG_TMS: U37.P$72 (PA13), U39.P$2 (2_SWDIO_TMS)
MISSING_BUTTON: U37.P$38 (PE7)
MOT0BEMFH: U37.P$23 (PA0); also elsewhere on the board
MOT0BEMFL: U37.P$24 (PA1); also elsewhere on the board
MOT0_D0: U37.P$82 (PD1); also elsewhere on the board
MOT0_D1: U37.P$88 (PD7); also elsewhere on the board
MOT0_PWM: U37.P$67 (PA8); also elsewhere on the board
MOT1BEMFH: U37.P$25 (PA2); also elsewhere on the board
MOT1BEMFL: U37.P$26 (PA3); also elsewhere on the board
MOT1_D0: U37.P$46 (PE15); also elsewhere on the board
MOT1_D1: U37.P$7 (PC13); also elsewhere on the board
MOT1_PWM: U37.P$68 (PA9); also elsewhere on the board
MOT2BEMFH: U37.P$29 (PA4); also elsewhere on the board
MOT2BEMFL: U37.P$30 (PA5); also elsewhere on the board
MOT2_D0: U37.P$8 (PC14); also elsewhere on the board
MOT2_D1: U37.P$9 (PC15); also elsewhere on the board
MOT2_PWM: U37.P$69 (PA10); also elsewhere on the board
MOT3BEMFH: U37.P$31 (PA6); also elsewhere on the board
MOT3BEMFL: U37.P$32 (PA7); also elsewhere on the board
MOT3_D0: U37.P$57 (PD10); also elsewhere on the board
MOT3_D1: U37.P$58 (PD11); also elsewhere on the board
MOT3_PWM: U37.P$63 (PC6); also elsewhere on the board
unnamed: C20.1, R29.2, U38.P$1 (OSC1)
unnamed: R66.1, U37.P$41 (PE10)
OSC_IN: C21.1, U37.P$12 (OSC_IN), U38.P$3 (OSC3)
OSC_OUT: R29.1, U37.P$13 (OSC_OUT)
PI_GPIO17: R45.2, U37.P$94 (BOOT0); also elsewhere on the board
PI_GPIO23: R48.2; also elsewhere on the board
PI_SPI0_CS0: U37.P$51 (PB12); also elsewhere on the board
PI_SPI0_MISO: U37.P$53 (PB14); also elsewhere on the board
PI_SPI0_MOSI: U37.P$54 (PB15); also elsewhere on the board
PI_SPI0_SCLK: U37.P$52 (PB13); also elsewhere on the board
PI_UART0_RX: U37.P$47 (PB10); also elsewhere on the board
PI_UART0_TX: U37.P$48 (PB11); also elsewhere on the board
S0_PWM_3V3: U37.P$65 (PC8); also elsewhere on the board
S1_PWM_3V3: U37.P$64 (PC7); also elsewhere on the board
S2_PWM_3V3: U37.P$5 (PE6); also elsewhere on the board
S3_PWM_3V3: U37.P$4 (PE5); also elsewhere on the board
STM_RESET: C34.1, R48.1, U37.P$14 (NRST), U39.P$10 (10_NRESET)
USER_LED: U37.P$40 (PE9); also elsewhere on the board
VCAP1: C37.1, U37.P$49 (VCAP1)
VCAP2: C38.1, U37.P$73 (VCAP2)
VCC_3V3: C32.1, C33.1, C36.1, C39.2, C40.2, C41.2, C42.2, C43.2, C44.1, C45.1, C46.1, U37.P$6 (VBAT_6), U37.P$11 (VDD_11), U37.P$19 (VDD_19), U37.P$21 (VREF+_21), U37.P$22 (VDDA_22), U37.P$28 (VDD_28), U37.P$50 (VDD_50), U37.P$75 (VDD_75), U37.P$100 (VDD_100), U39.P$1 (1_VCC); also elsewhere on the board
VCC_BATT_RAW: R64.2; also elsewhere on the board
VCC_BATT_SENSE: R64.1, R65.2, U37.P$15 (PC0)

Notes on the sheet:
Microcontroller

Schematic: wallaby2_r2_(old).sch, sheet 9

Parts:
C22: 0.1uF; 0603-CAP
R11: 10K; 0603-RES
U42: COINCELL_6P8MM; COIN_CELL_HOLDER_6P8MM
U43: DS1340U; USOP-8
U44: CRYSTAL-ECS-ECX34B; CRYSTAL-ECX34B-3P2MM_1P5MM

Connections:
GND: C22.1, U42.P_MIN, U43.P$4 (4_GND); also elsewhere on the board
unnamed: U42.P_PLUS_1, U42.P_PLUS_2, U43.P$3 (3_VBAT)
unnamed: U43.P$2 (2_X2), U44.P$2
unnamed: U43.P$1 (1_X1), U44.P$1
unnamed: R11.1, U43.P$7 (7_OUT)
PI_I2C1_SCL: U43.P$6 (6_SCL); also elsewhere on the board
PI_I2C1_SDA: U43.P$5 (5_SDA); also elsewhere on the board
VCC_3V3: C22.2, R11.2, U43.P$8 (8_VCC); also elsewhere on the board

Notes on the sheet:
RTC and Battery Backup

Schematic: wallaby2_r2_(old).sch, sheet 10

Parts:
C26, C27: 0.1uF; 0603-CAP
U30, U41, U76, U77: CONN-HEADER-5-103414-1; HEADER-5-103414-1
U56: TXS0104; TSSOP14
U68, U69, U70, U71: FUSE-RESET-0603L100SLYR; 0603

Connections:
GND: C26.2, C27.2, U30.P$3, U41.P$3, U56.P$7 (7_GND), U76.P$3, U77.P$3; also elsewhere on the board
unnamed: U71.P$2, U77.P$2
unnamed: U70.P$2, U76.P$2
unnamed: U30.P$2, U68.P$2
unnamed: U41.P$2, U69.P$2
S0_PWM_3V3: U56.P$5 (5_A4); also elsewhere on the board
S0_PWM_5V0: U30.P$1, U56.P$10 (10_B4)
S1_PWM_3V3: U56.P$4 (4_A3); also elsewhere on the board
S1_PWM_5V0: U41.P$1, U56.P$11 (11_B3)
S2_PWM_3V3: U56.P$3 (3_A2); also elsewhere on the board
S2_PWM_5V0: U56.P$12 (12_B2), U76.P$1
S3_PWM_3V3: U56.P$2 (2_A1); also elsewhere on the board
S3_PWM_5V0: U56.P$13 (13_B1), U77.P$1
VCC_3V3: C27.1, U56.P$1 (1_VCCA), U56.P$8 (8_OE); also elsewhere on the board
VCC_5V0: C26.1, U56.P$14 (14_VCCB); also elsewhere on the board
VCC_6V0: U68.P$1, U69.P$1, U70.P$1, U71.P$1; also elsewhere on the board

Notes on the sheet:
Servos

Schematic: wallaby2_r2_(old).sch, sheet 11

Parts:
C28, C31, C48, C51: 0.1uF 20V; 0603-CAP
C29, C30, C49, C50: 10uF 20V; 0603-CAP
C35, C47, C52, C53: 22pf; 0603-CAP
J8, J10: FEMALE 2x3; 2X3
R12, R13, R28, R31: 1K; 0603-RES
R14, R17, R18, R19, R33, R34, R35, R36: 470R; 0603-RES
R20, R21, R24, R25, R39, R40, R43, R44: 2k2; 0603-RES
R22, R23, R26, R27, R41, R42, R46, R47: 6k8; 0603-RES
U61, U64: TB6612FNG; SSOP24
U62, U63, U65, U66: APB3025ESGC-F01; DUAL_SMT_LED

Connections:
GND: C28.2, C29.2, C30.2, C31.2, C48.2, C49.2, C50.2, C51.2, R17.1, R19.1, R34.1, R36.1, U61.P$3 (PGND1_3), U61.P$4 (PGND1_4), U61.P$9 (PGND2_9), U61.P$10 (PGND2_10), U61.P$18 (GND_18), U64.P$3 (PGND1_3), U64.P$4 (PGND1_4), U64.P$9 (PGND2_9), U64.P$10 (PGND2_10), U64.P$18 (GND_18); also elsewhere on the board
MOT0A: J8.2, J8.4, R26.2, U61.P$1 (AO1_1), U61.P$2 (AO1_2), U63.P$2, U63.P$3
MOT0B: J8.6, R12.1, R27.2, U61.P$5 (AO2_5), U61.P$6 (AO2_6)
MOT0BEMFH: C47.2, R24.2, R26.1; also elsewhere on the board
MOT0BEMFL: C47.1, R25.2, R27.1; also elsewhere on the board
MOT0_D0: U61.P$21 (AIN1_21); also elsewhere on the board
MOT0_D1: U61.P$22 (AIN2_22); also elsewhere on the board
MOT0_PWM: U61.P$23 (PWMA_23); also elsewhere on the board
MOT1A: J8.1, J8.3, R22.2, U61.P$11 (BO1_11), U61.P$12 (BO1_12), U62.P$2, U62.P$3
MOT1B: J8.5, R13.2, R23.2, U61.P$7 (BO2_7), U61.P$8 (BO2_8)
MOT1BEMFH: C35.2, R20.2, R22.1; also elsewhere on the board
MOT1BEMFL: C35.1, R21.2, R23.1; also elsewhere on the board
MOT1_D0: U61.P$17 (BIN1_17); also elsewhere on the board
MOT1_D1: U61.P$16 (BIN2_16); also elsewhere on the board
MOT1_PWM: U61.P$15 (PWMB_15); also elsewhere on the board
MOT2A: J10.2, J10.4, R46.2, U64.P$1 (AO1_1), U64.P$2 (AO1_2), U66.P$2, U66.P$3
MOT2B: J10.6, R28.1, R47.2, U64.P$5 (AO2_5), U64.P$6 (AO2_6)
MOT2BEMFH: C53.2, R43.2, R46.1; also elsewhere on the board
MOT2BEMFL: C53.1, R44.2, R47.1; also elsewhere on the board
MOT2_D0: U64.P$21 (AIN1_21); also elsewhere on the board
MOT2_D1: U64.P$22 (AIN2_22); also elsewhere on the board
MOT2_PWM: U64.P$23 (PWMA_23); also elsewhere on the board
MOT3A: J10.1, J10.3, R41.2, U64.P$11 (BO1_11), U64.P$12 (BO1_12), U65.P$2, U65.P$3
MOT3B: J10.5, R31.2, R42.2, U64.P$7 (BO2_7), U64.P$8 (BO2_8)
MOT3BEMFH: C52.2, R39.2, R41.1; also elsewhere on the board
MOT3BEMFL: C52.1, R40.2, R42.1; also elsewhere on the board
MOT3_D0: U64.P$17 (BIN1_17); also elsewhere on the board
MOT3_D1: U64.P$16 (BIN2_16); also elsewhere on the board
MOT3_PWM: U64.P$15 (PWMB_15); also elsewhere on the board
N22: R13.1, U62.P$1, U62.P$4
N43: R31.1, U65.P$1, U65.P$4
N44: R28.2, U66.P$1, U66.P$4
unnamed: R12.2, U63.P$1, U63.P$4
unnamed: R18.1, R19.2, R20.1, R21.1
unnamed: R14.1, R17.2, R24.1, R25.1
unnamed: R35.1, R36.2, R39.1, R40.1
unnamed: R33.1, R34.2, R43.1, R44.1
VCC_3V3: C30.1, C31.1, C50.1, C51.1, R14.2, R18.2, R33.2, R35.2, U61.P$19 (STBY_19), U61.P$20 (VCC_20), U64.P$19 (STBY_19), U64.P$20 (VCC_20); also elsewhere on the board
VCC_BATT_FUSE: C28.1, C29.1, C48.1, C49.1, U61.P$13 (VM2_13), U61.P$14 (VM3_14), U61.P$24 (VM1_24), U64.P$13 (VM2_13), U64.P$14 (VM3_14), U64.P$24 (VM1_24); also elsewhere on the board

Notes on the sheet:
Motors

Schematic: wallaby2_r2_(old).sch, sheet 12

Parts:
C54: 0.1uF 20V; 0603-CAP
U67: AT24CS01-STUM-T; SOT-23-5

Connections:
GND: C54.2, U67.P$2 (2_GND), U67.P$5 (5_WP); also elsewhere on the board
PI_I2C1_SCL: U67.P$1 (1_SCL); also elsewhere on the board
PI_I2C1_SDA: U67.P$3 (3_SDA); also elsewhere on the board
VCC_3V3: C54.1, U67.P$4 (4_VCC); also elsewhere on the board

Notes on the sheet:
EEPROM Address 0x50

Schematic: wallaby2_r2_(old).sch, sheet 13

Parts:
C69, C70: 0.1uF; 0603
C71: 10pF; 0603
U5: 9DoF IMU; QFN24-3X3

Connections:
GND: C69.2, C70.2, C71.2, U5.11 (FSYNC), U5.18 (GND), U5.20 (GND); also elsewhere on the board
IMU_SPI_CLK: U5.23 (SCL/SCLK); also elsewhere on the board
IMU_SPI_CS0: U5.22 (!CS); also elsewhere on the board
IMU_SPI_MISO: U5.9 (AD0/SDO); also elsewhere on the board
IMU_SPI_MOSI: U5.24 (SDA/SDI); also elsewhere on the board
unnamed: C70.1, U5.10 (REGOUT)
VCC_3V3: C69.1, C71.1, U5.1 (VDDIO), U5.8 (VDDIO), U5.13 (VDD); also elsewhere on the board

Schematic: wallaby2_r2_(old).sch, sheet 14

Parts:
D4: red; LED-0603
Q1, Q2: BSP170P; SOT223
R10: 1K; 0603-RES
R37: 3K3; 0603-RES
R38: 100K; 0603-RES
U3: XT60; XT60-FP-MH
U35: SWITCH-OS102011MA1QN1; OS-SPDT-MINI-SLIDE_SWITCH
U74: 2920L500-16MR; FUSE-2920

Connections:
GND: R10.1, U3.NEG (CONN_N), U35.P$1; also elsewhere on the board
unnamed: D4.C, R10.2
unnamed: R37.2, U35.P$2
unnamed: Q1.1 (G), Q2.1 (G), R37.1, R38.2
VCC_3V3: D4.A; also elsewhere on the board
VCC_BATT_FUSE: U74.P$2; also elsewhere on the board
VCC_BATT_NO_FUSE: Q1.2 (D), Q1.4 (D); also elsewhere on the board
VCC_BATT_PRE_FUSE: Q2.2 (D), Q2.4 (D), U74.P$1
VCC_BATT_RAW: Q1.3 (S), Q2.3 (S), R38.1, U3.POS (CONN_P); also elsewhere on the board

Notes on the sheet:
Power

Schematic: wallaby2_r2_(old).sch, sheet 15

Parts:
C14: 10uF; 0603
C15: 0.1uF; 0603
C23, C72: 22pF; 0603
FB5, FB6: Ferrite; _0805MP
J4: CONN_02; 1X02
R61: 1M; 0603
R62, R63: DNP; 0603
U45: MAX98357; TQFN-16

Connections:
GND: C14.2, C15.2, C23.2, C72.2, R63.1, U45.GND, U45.P$3 (GND), U45.P$11 (GND), U45.P$15 (GND); also elsewhere on the board
I2S_BCLK: U45.P$16 (BCLK); also elsewhere on the board
I2S_DIN: U45.P$1 (DIN); also elsewhere on the board
I2S_LRCLK: U45.P$14 (LRCLK); also elsewhere on the board
unnamed: FB5.1, U45.P$9 (OUTP)
unnamed: FB6.1, U45.P$10 (OUTN)
unnamed: C23.1, FB5.2, J4.1
unnamed: C72.1, FB6.2, J4.2
unnamed: R61.1, U45.P$4 (SD)
unnamed: R62.1, R63.2, U45.P$2 (GAIN)
VCC_5V0: C14.1, C15.1, R61.2, R62.2, U45.P$7 (VDD), U45.P$8 (VDD); also elsewhere on the board

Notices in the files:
README.md:
License: GPL v3
parts and their libraries:
microbuilder: This work is placed in the public domain, and may be freely used for commercial and non-commercial work with the following conditions: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
SparkFun-Capacitors: Licensing: Creative Commons ShareAlike 4.0 International - https://creativecommons.org/licenses/by-sa/4.0
